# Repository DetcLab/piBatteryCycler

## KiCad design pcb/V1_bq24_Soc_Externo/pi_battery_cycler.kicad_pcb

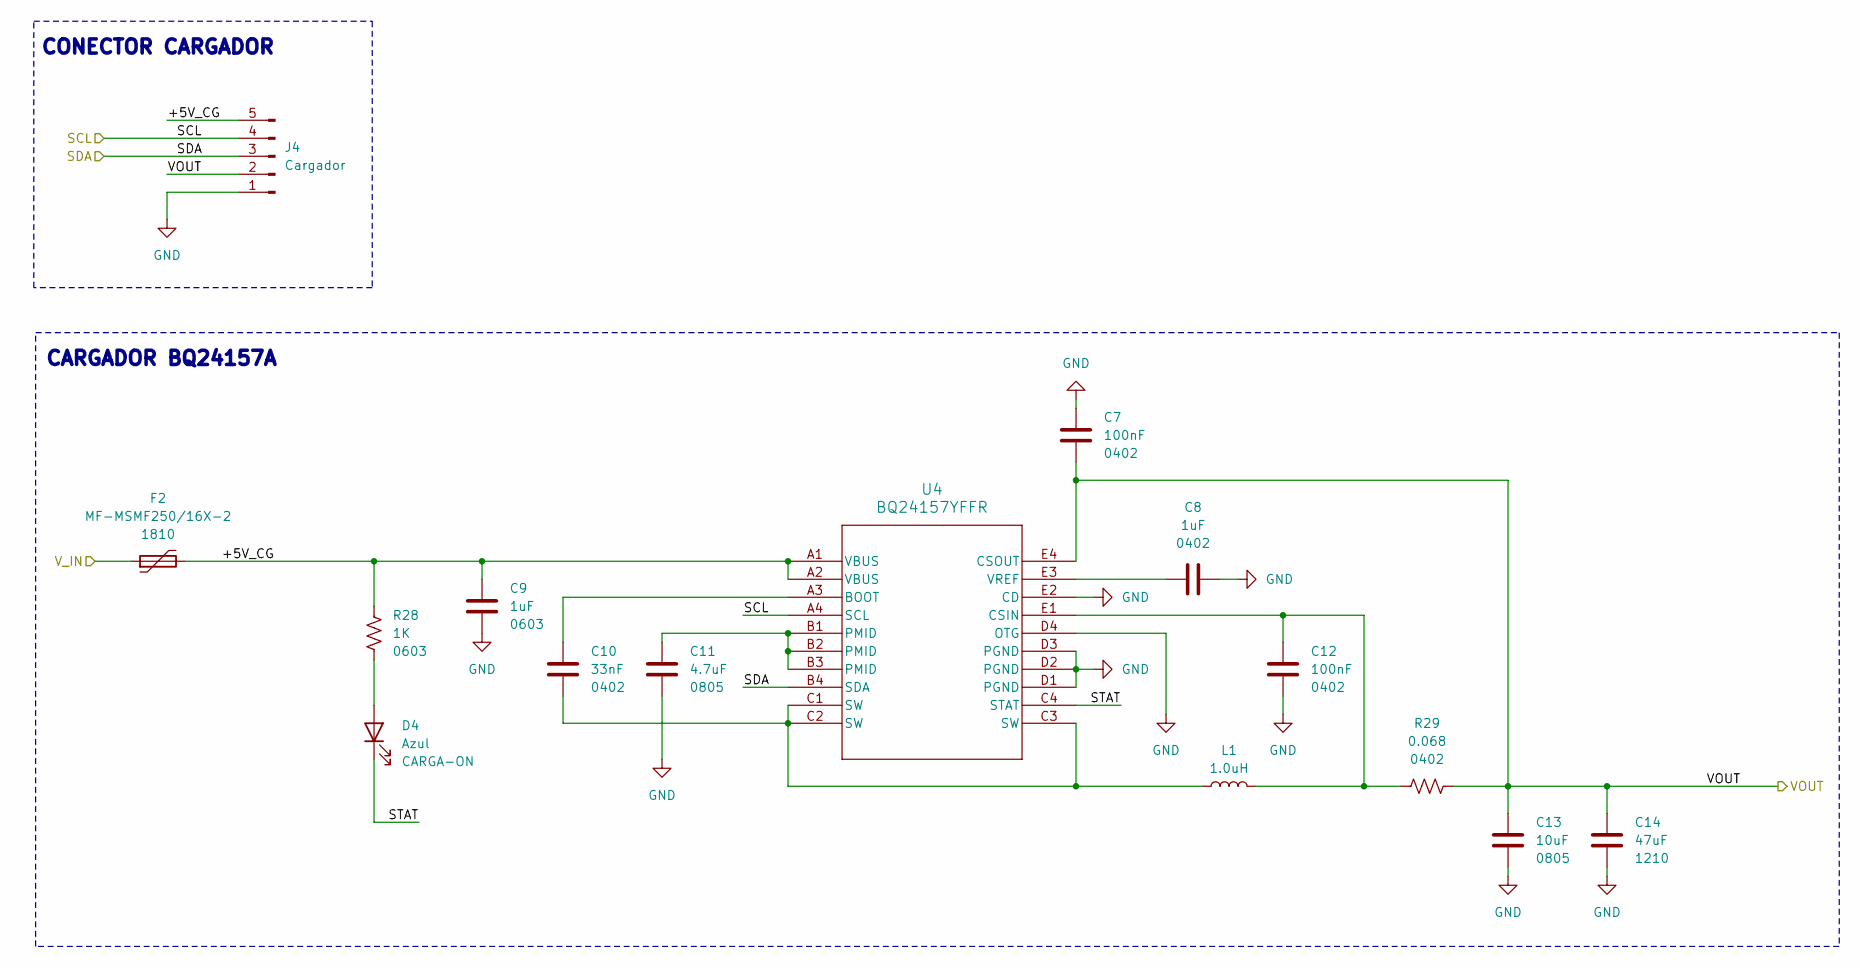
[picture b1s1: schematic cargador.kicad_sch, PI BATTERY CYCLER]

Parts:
C7, C12: 100nF; C_0402_1005Metric; MPN GRM155R71C104KA88D; Digikey 490-3261-2-ND
C8: 1uF; C_0402_1005Metric; MPN CL05A105KP5NNNC; Digikey 1276-1076-2-ND
C9: 1uF; C_0603_1608Metric_Pad1.08x0.95mm_HandSolder; MPN GRM188R61C105KA12D; Digikey 490-10479-2-ND
C10: 33nF; C_0402_1005Metric; MPN GRM155R61C333KA01D; Digikey 490-5416-2-ND
C11: 4.7uF; C_0805_2012Metric; MPN GRM21BR71C475KE51L; Digikey 490-14466-2-ND
C13: 10uF; C_0805_2012Metric; MPN CL21A106KOQNNNE; Digikey 1276-1096-2-ND
C14: 47uF; C_1210_3225Metric; MPN GRM32ER61A476KE20L; Digikey 490-3887-2-ND
D4: Azul; LED_0603_1608Metric; MPN 150060BS75000; Digikey 732-4966-2-ND
F2: MF-MSMF250/16X-2; Fuse_1812_4532Metric; MPN MF-MSMF250/16X-2; Digikey MF-MSMF250/16X-2TR-ND
J4: Cargador; JST_XH_B5B-XH-A_1x05_P2.50mm_Vertical
L1: 1.0uH; L_1008_2520Metric; MPN LQM2HPN1R0MJ0L; Digikey 490-6699-2-ND
R28: 1K; R_0603_1608Metric_Pad0.98x0.95mm_HandSolder; MPN RC0603FR-071KL; Digikey 311-1.00KHRTR-ND
R29: 0.068; R_0402_1005Metric; MPN ERJ-2BWJR068X; Digikey P.068AMTR-ND
U4: BQ24157YFFR; YFF20_TEX; MPN BQ24157YFFR; Digikey 296-39908-2-ND

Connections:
/CARGADOR/+5V_CG: C9.2, F2.2, J4.5, R28.1, U4.A1 (VBUS), U4.A2 (VBUS)
/CARGADOR/SCL: J4.4, U4.A4 (SCL); also elsewhere on the board
/CARGADOR/SDA: J4.3, U4.B4 (SDA); also elsewhere on the board
/CARGADOR/STAT: D4.1 (K), U4.C4 (STAT)
/CARGADOR/VOUT: C7.1, C13.2, C14.2, J4.2, R29.2, U4.E4 (CSOUT); also elsewhere on the board
/CARGADOR/V_IN: F2.1; also elsewhere on the board
GND: C7.2, C8.2, C9.1, C11.2, C12.1, C13.1, C14.1, J4.1, U4.D1 (PGND), U4.D2 (PGND), U4.D3 (PGND), U4.D4 (OTG), U4.E2 (CD); also elsewhere on the board
unnamed: C10.1, L1.1, U4.C1 (SW), U4.C2 (SW), U4.C3 (SW)
unnamed: C11.1, U4.B1 (PMID), U4.B2 (PMID), U4.B3 (PMID)
unnamed: D4.2 (A), R28.2
unnamed: C10.2, U4.A3 (BOOT)
unnamed: C12.2, L1.2, R29.1, U4.E1 (CSIN)
unnamed: C8.1, U4.E3 (VREF)

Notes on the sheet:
CONECTOR CARGADOR
CARGADOR BQ24157A

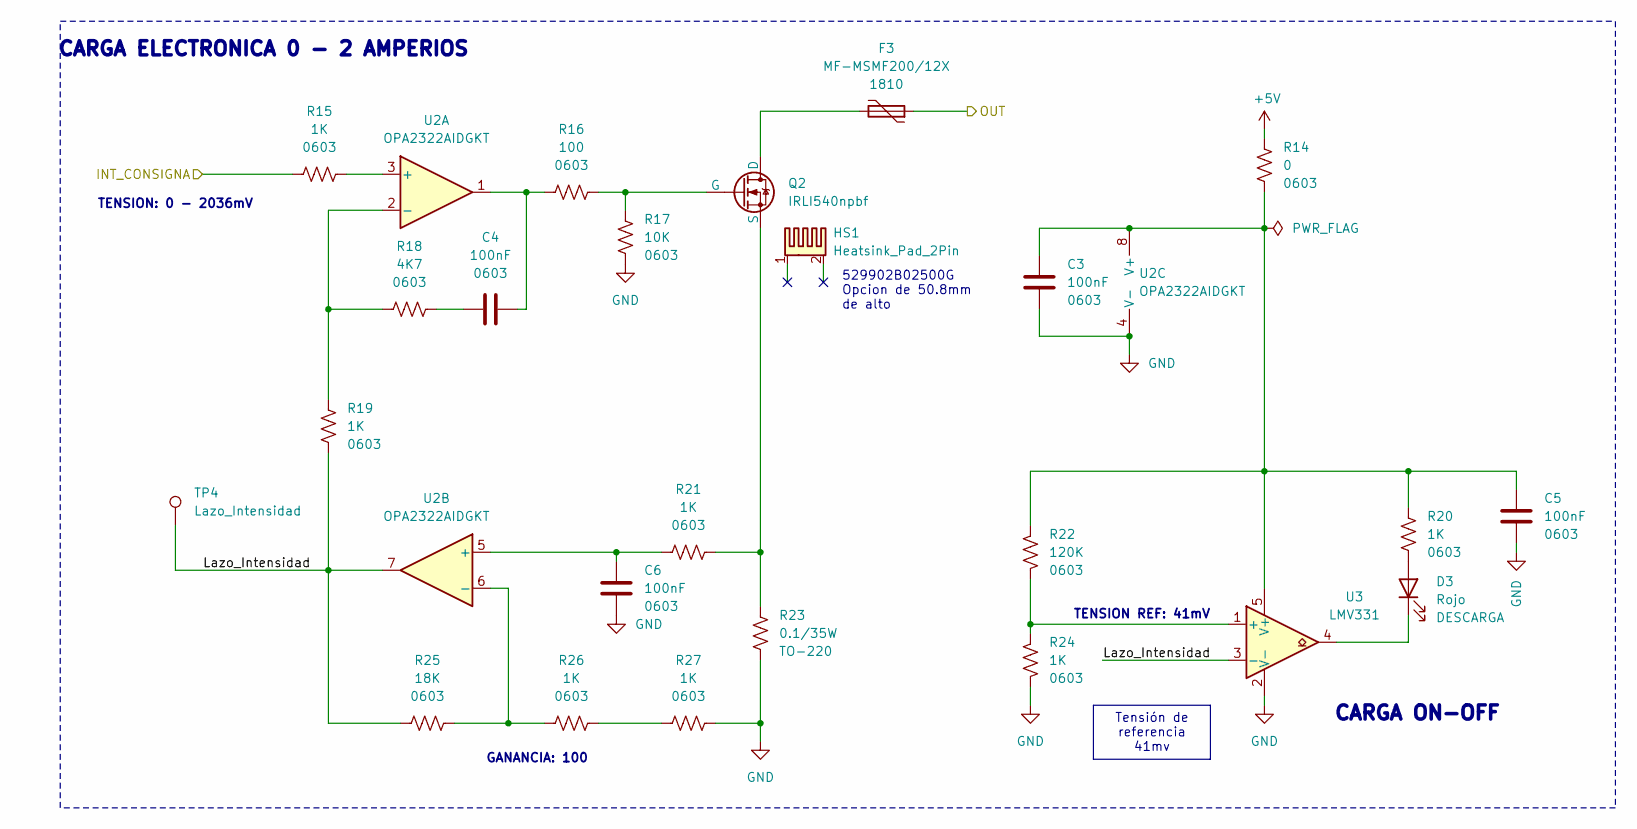
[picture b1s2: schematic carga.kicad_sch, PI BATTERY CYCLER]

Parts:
C3, C4, C5, C6: 100nF; C_0603_1608Metric_Pad1.08x0.95mm_HandSolder; MPN CL10B104KB8NNNC; Digikey 1276-1000-2-ND
D3: Rojo; LED_0603_1608Metric; MPN 150060RS75000; Digikey 732-4978-2-ND
F3: MF-MSMF200/12X; Fuse_1812_4532Metric; MPN MF-MSMF200/12X-2; Digikey 118-MF-MSMF200/12X-2TR-ND
HS1: Heatsink_Pad_2Pin; Heatsink_25.4x41.91mm_Aavid_529802B02500G; Digikey HS374-ND
Q2: IRLI540npbf; TO-220-3_Vertical; Digikey IRL540NPBF-ND
R14: 0; R_0603_1608Metric_Pad0.98x0.95mm_HandSolder; MPN RC0603FR-070RL; Digikey 311-0.0HRTR-ND
R15, R19, R20, R21, R24, R26, R27: 1K; R_0603_1608Metric_Pad0.98x0.95mm_HandSolder; MPN RC0603FR-071KL; Digikey 311-1.00KHRTR-ND
R16: 100; R_0603_1608Metric_Pad0.98x0.95mm_HandSolder; MPN RC0603FR-07100RL; Digikey 311-100HRTR-ND
R17: 10K; R_0603_1608Metric_Pad0.98x0.95mm_HandSolder; MPN RC0603FR-0710KL; Digikey 311-10.0KHRTR-ND
R18: 4K7; R_0603_1608Metric_Pad0.98x0.95mm_HandSolder; MPN RC0603FR-074K7L; Digikey 311-4.70KHRTR-ND
R22: 120K; R_0603_1608Metric_Pad0.98x0.95mm_HandSolder; MPN RC0603FR-07120KL; Digikey 311-120KHRTR-ND
R23: 0.1/35W; TO-220-2_Vertical; Digikey 696-1161-ND
R25: 18K; R_0603_1608Metric_Pad0.98x0.95mm_HandSolder; MPN RC0603FR-0718KL; Digikey 311-18.0KHRTR-ND
TP4: Lazo_Intensidad; TestPoint_Pad_D1.0mm
U2: OPA2322AIDGKT; VSSOP-8_3x3mm_P0.65mm; MPN OPA2322AIDGKT; Digikey 296-28774-2-ND
U3: LMV331; SOT-353_SC-70-5; MPN LMV331IDCKR; Digikey 296-6634-2-ND

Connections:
+5V: R14.1; also elsewhere on the board
/CARGA/INT_CONSIGNA: R15.2; also elsewhere on the board
/CARGA/Lazo_Intensidad: R19.2, R25.2, TP4.1 (1_1), U2.7, U3.3 (-)
/CARGADOR/VOUT: F3.1; also elsewhere on the board
GND: C3.2, C5.2, C6.2, R17.1, R23.2, R24.2, R27.1, U2.4 (V-), U3.2 (V-); also elsewhere on the board
unnamed: C4.1, R18.2
unnamed: C4.2, R16.1, U2.1
unnamed: D3.2 (A), R20.2
unnamed: D3.1 (K), U3.4
unnamed: F3.2, Q2.2 (D)
unnamed: Q2.1 (G), R16.2, R17.2
unnamed: Q2.3 (S), R21.1, R23.1
unnamed: R26.1, R27.2
unnamed: R15.1, U2.3 (+)
unnamed: R18.1, R19.1, U2.2 (-)
unnamed: C6.1, R21.2, U2.5 (+)
unnamed: R25.1, R26.2, U2.6 (-)
unnamed: C3.1, C5.1, R14.2, R20.1, R22.1, U2.8 (V+), U3.5 (V+)
unnamed: R22.2, R24.1, U3.1 (+)

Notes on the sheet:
529902B02500G Opcion de 50.8mm de alto
TENSION: 0 - 2036mV
CARGA ELECTRONICA 0 - 2 AMPERIOS
CARGA ON-OFF
TENSION REF: 41mV
GANANCIA: 100
Tensión de referencia 41mv

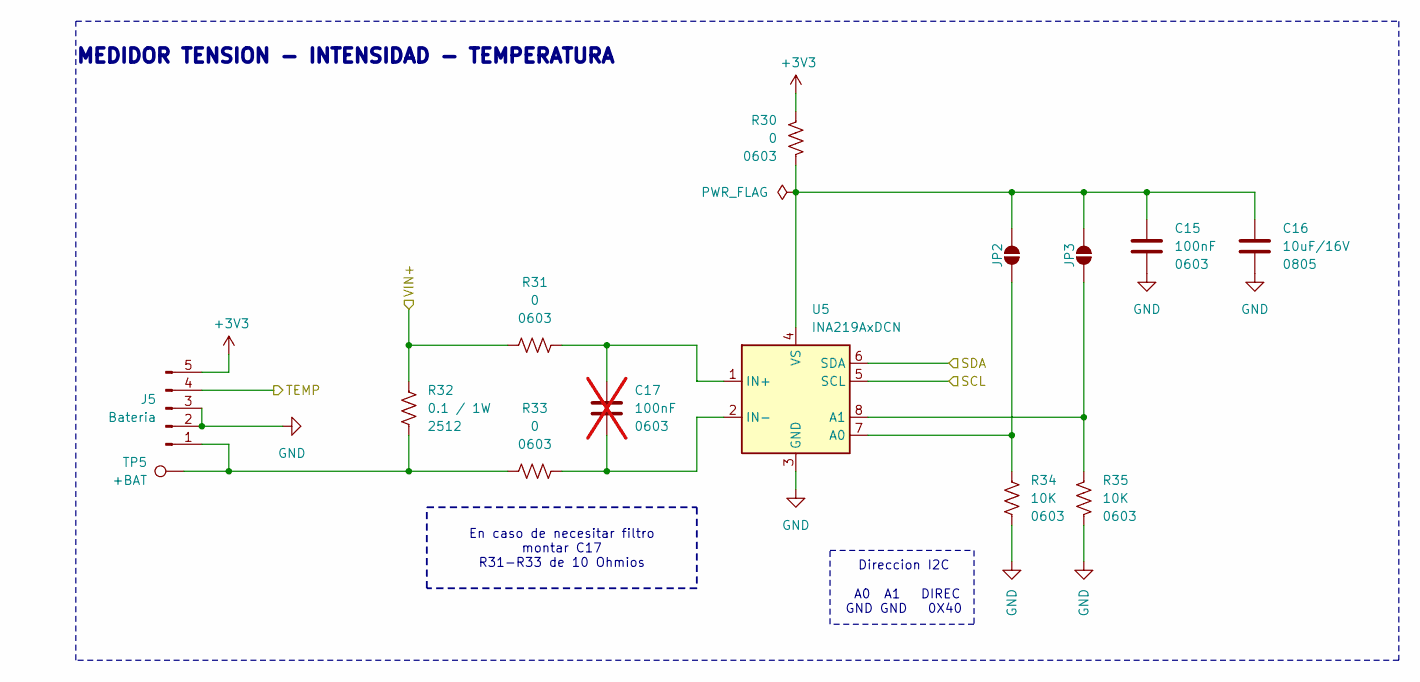
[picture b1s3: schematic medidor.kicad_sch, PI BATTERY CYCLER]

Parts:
C15: 100nF; C_0603_1608Metric_Pad1.08x0.95mm_HandSolder; MPN CL10B104KB8NNNC; Digikey 1276-1000-2-ND
C16: 10uF/16V; C_0805_2012Metric; MPN CL21A106KOQNNNE; Digikey 1276-1096-2-ND
C17: 100nF; C_0603_1608Metric_Pad1.08x0.95mm_HandSolder; MPN CL10B104KB8NNNC; Digikey 1276-1000-2-ND; not fitted
J5: Bateria; JST_XH_B5B-XH-A_1x05_P2.50mm_Vertical
JP2, JP3: SolderJumper_2_Open; SolderJumper-2_P1.3mm_Open_RoundedPad1.0x1.5mm
R30, R31, R33: 0; R_0603_1608Metric_Pad0.98x0.95mm_HandSolder; MPN RC0603FR-070RL; Digikey 311-0.0HRTR-ND
R32: 0.1 / 1W; R_2512_6332Metric; Part Number PE2512FKE070R1L; Digikey YAG2159TR-ND
R34, R35: 10K; R_0603_1608Metric_Pad0.98x0.95mm_HandSolder; MPN RC0603FR-0710KL; Digikey 311-10.0KHRTR-ND
TP5: +BAT; TestPoint_Pad_D1.0mm
U5: INA219AxDCN; SOT-23-8

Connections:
+3V3: J5.5, R30.1; also elsewhere on the board
/CARGADOR/SCL: U5.5 (SCL); also elsewhere on the board
/CARGADOR/SDA: U5.6 (SDA); also elsewhere on the board
/CARGADOR/VOUT: R31.1, R32.1; also elsewhere on the board
/MEDIDOR/TEMP: J5.4; also elsewhere on the board
GND: C15.2, C16.2, J5.2, J5.3, R34.2, R35.2, U5.3 (GND); also elsewhere on the board
unnamed: J5.1, R32.2, R33.1, TP5.1 (1_1)
unnamed: JP2.1 (A), R34.1, U5.7 (A0)
unnamed: C15.1, C16.1, JP2.2 (B), JP3.2 (B), R30.2, U5.4 (VS)
unnamed: JP3.1 (A), R35.1, U5.8 (A1)
unnamed: C17.2, R31.2, U5.1 (IN+)
unnamed: C17.1, R33.2, U5.2 (IN-)

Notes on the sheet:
Direccion I2C A0 A1 DIREC GND GND 0X40
MEDIDOR TENSION - INTENSIDAD - TEMPERATURA
En caso de necesitar filtro montar C17 R31-R33 de 10 Ohmios

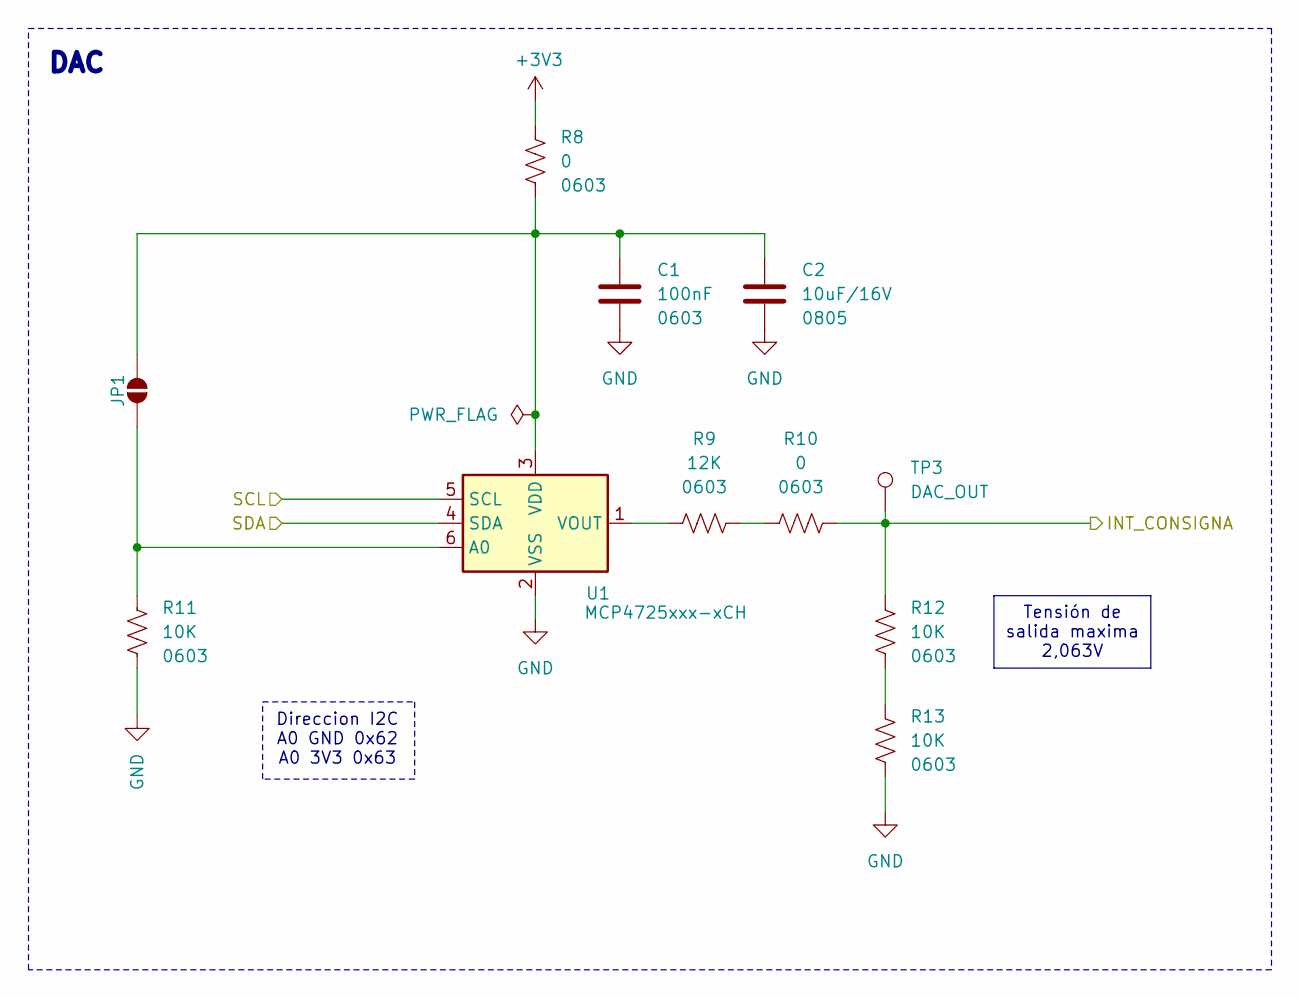
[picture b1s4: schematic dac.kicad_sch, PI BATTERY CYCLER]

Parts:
C1: 100nF; C_0603_1608Metric_Pad1.08x0.95mm_HandSolder; MPN CL10B104KB8NNNC; Digikey 1276-1000-2-ND
C2: 10uF/16V; C_0805_2012Metric; MPN CL21A106KOQNNNE; Digikey 1276-1096-2-ND
JP1: SolderJumper_2_Open; SolderJumper-2_P1.3mm_Open_RoundedPad1.0x1.5mm
R8, R10: 0; R_0603_1608Metric_Pad0.98x0.95mm_HandSolder; MPN RC0603FR-070RL; Digikey 311-0.0HRTR-ND
R9: 12K; R_0603_1608Metric_Pad0.98x0.95mm_HandSolder; MPN RC0603FR-0712KL; Digikey 311-12.0KHRTR-ND
R11, R12, R13: 10K; R_0603_1608Metric_Pad0.98x0.95mm_HandSolder; MPN RC0603FR-0710KL; Digikey 311-10.0KHRTR-ND
TP3: DAC_OUT; TestPoint_Pad_D1.0mm
U1: MCP4725xxx-xCH; SOT-23-6; MPN MCP4725A0T-E/CH; Digikey MCP4725A0T-E/CHCT-ND

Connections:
+3V3: R8.1; also elsewhere on the board
/CARGA/INT_CONSIGNA: R10.2, R12.2, TP3.1 (1_1); also elsewhere on the board
/CARGADOR/SCL: U1.5 (SCL); also elsewhere on the board
/CARGADOR/SDA: U1.4 (SDA); also elsewhere on the board
GND: C1.2, C2.2, R11.2, R13.1, U1.2 (VSS); also elsewhere on the board
unnamed: JP1.1 (A), R11.1, U1.6 (A0)
unnamed: C1.1, C2.1, JP1.2 (B), R8.2, U1.3 (VDD)
unnamed: R9.2, R10.1
unnamed: R12.1, R13.2
unnamed: R9.1, U1.1 (VOUT)

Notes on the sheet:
DAC
Direccion I2C A0 GND 0x62 A0 3V3 0x63
Tensión de salida maxima 2,063V

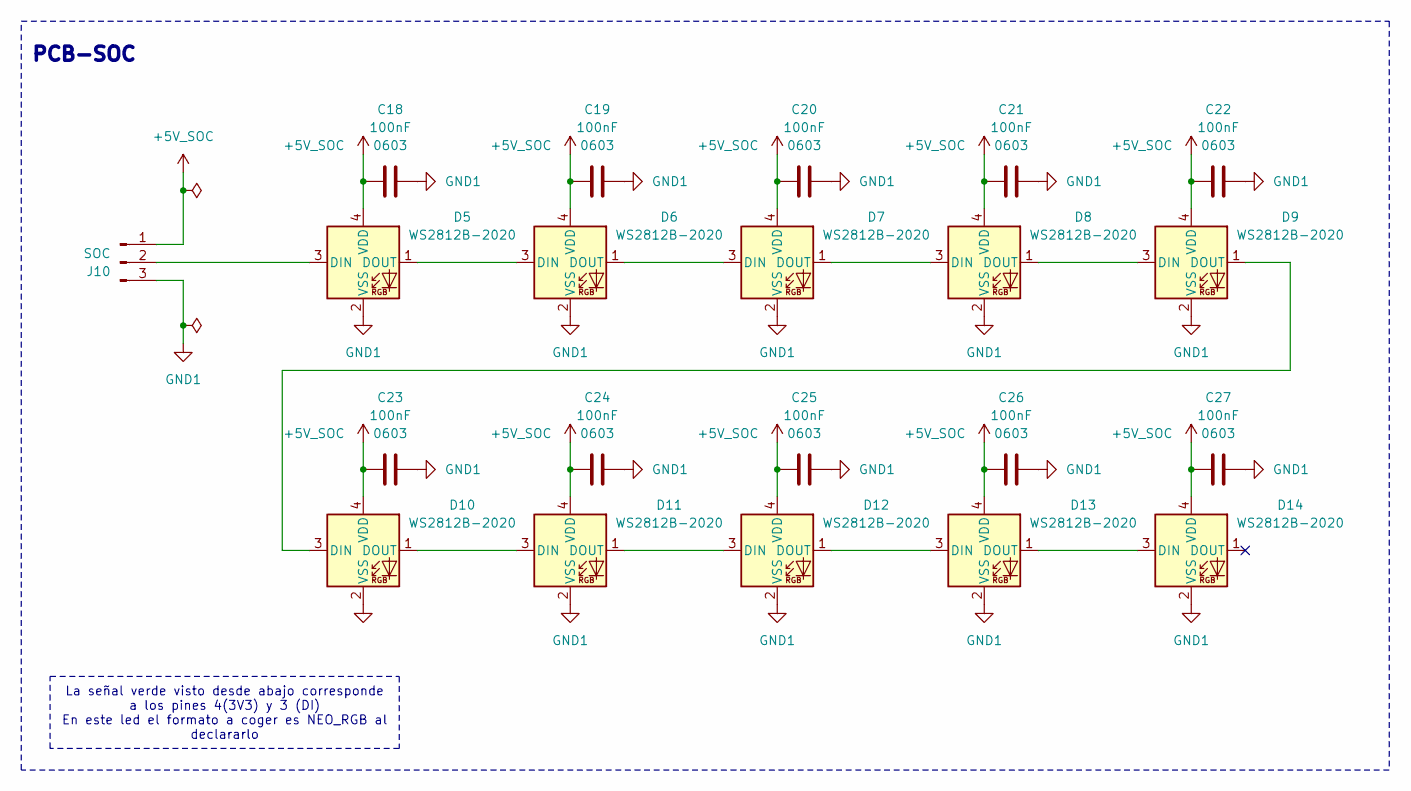
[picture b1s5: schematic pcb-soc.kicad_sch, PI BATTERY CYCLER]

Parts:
C18, C19, C20, C21, C22, C23, C24, C25, C26, C27: 100nF; C_0603_1608Metric_Pad1.08x0.95mm_HandSolder; MPN CL10B104KB8NNNC; Digikey 1276-1000-2-ND
D5, D6, D7, D8, D9, D10, D11, D12, D13, D14: WS2812B-2020; LED_WS2812B-2020_PLCC4_2.0x2.0mm; MPN 4684; Digikey 1528-4684-ND
J10: SOC; PinHeader_1x03_P2.54mm_Vertical

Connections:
+5V_SOC: C18.1, C19.1, C20.1, C21.1, C22.1, C23.1, C24.1, C25.1, C26.1, C27.1, D5.4 (VDD), D6.4 (VDD), D7.4 (VDD), D8.4 (VDD), D9.4 (VDD), D10.4 (VDD), D11.4 (VDD), D12.4 (VDD), D13.4 (VDD), D14.4 (VDD), J10.1
GND1: C18.2, C19.2, C20.2, C21.2, C22.2, C23.2, C24.2, C25.2, C26.2, C27.2, D5.2 (VSS), D6.2 (VSS), D7.2 (VSS), D8.2 (VSS), D9.2 (VSS), D10.2 (VSS), D11.2 (VSS), D12.2 (VSS), D13.2 (VSS), D14.2 (VSS), J10.3
unnamed: D5.3 (DIN), J10.2
unnamed: D5.1 (DOUT), D6.3 (DIN)
unnamed: D6.1 (DOUT), D7.3 (DIN)
unnamed: D7.1 (DOUT), D8.3 (DIN)
unnamed: D8.1 (DOUT), D9.3 (DIN)
unnamed: D9.1 (DOUT), D10.3 (DIN)
unnamed: D10.1 (DOUT), D11.3 (DIN)
unnamed: D11.1 (DOUT), D12.3 (DIN)
unnamed: D12.1 (DOUT), D13.3 (DIN)
unnamed: D13.1 (DOUT), D14.3 (DIN)

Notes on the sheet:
PCB-SOC
La señal verde visto desde abajo corresponde a los pines 4(3V3) y 3 (DI) En este led el formato a coger es NEO_RGB al declararlo

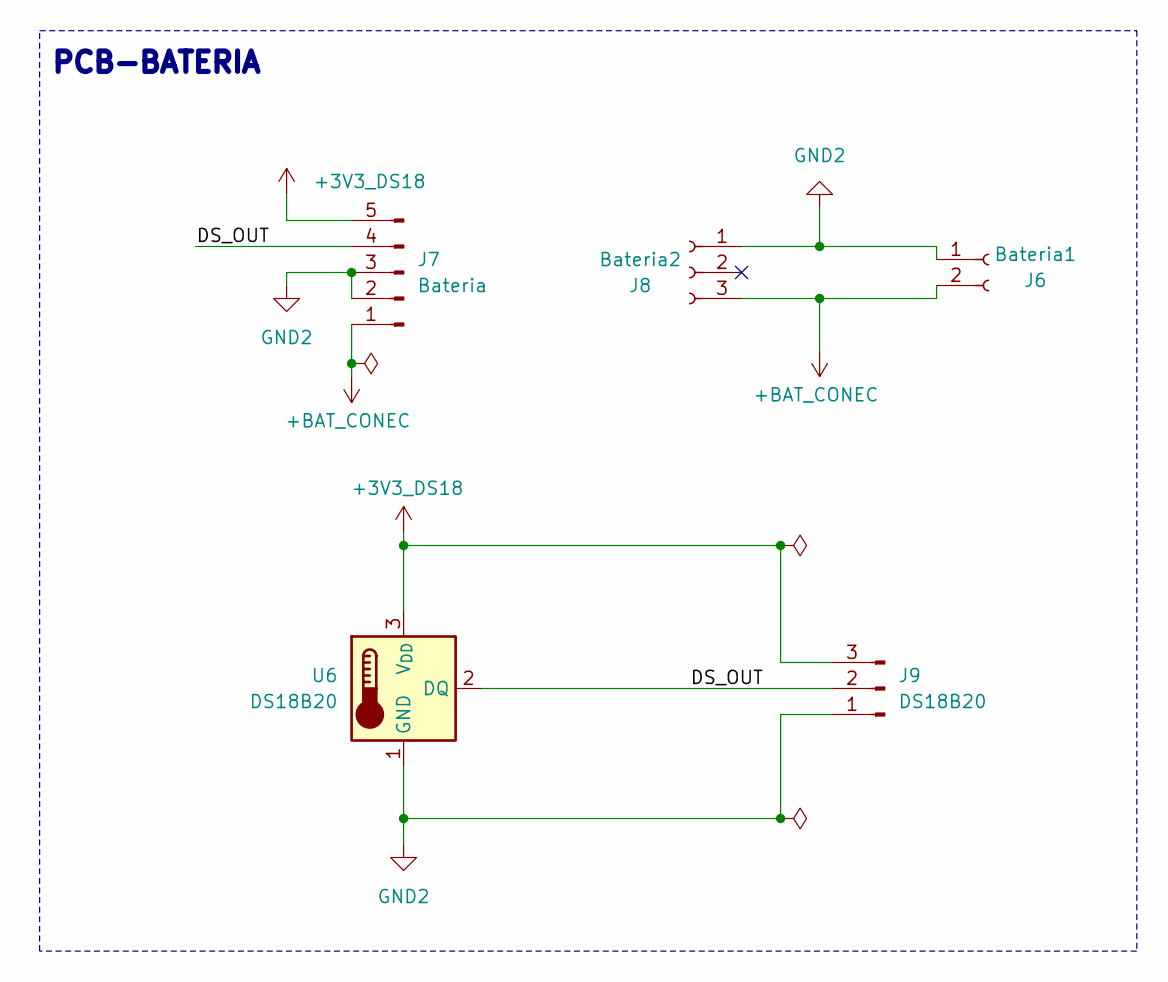
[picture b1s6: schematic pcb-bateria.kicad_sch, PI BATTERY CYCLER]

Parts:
J6: Bateria1; JST_XH_B2B-XH-A_1x02_P2.50mm_Vertical
J7: Bateria; PinHeader_1x05_P2.54mm_Vertical
J8: Bateria2; JST_XH_B3B-XH-A_1x03_P2.50mm_Vertical
J9: DS18B20; PinHeader_1x03_P2.54mm_Vertical
U6: DS18B20; TO-92_Inline; Digikey DS18B20+-ND

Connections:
+3V3_DS18: J7.5, J9.3, U6.3 (V_{DD})
+BAT_CONEC: J6.2, J7.1, J8.3
/PCB-BATERIA/DS_OUT: J7.4, J9.2, U6.2 (DQ)
GND2: J6.1, J7.2, J7.3, J8.1, J9.1, U6.1 (GND)

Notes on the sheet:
PCB-BATERIA

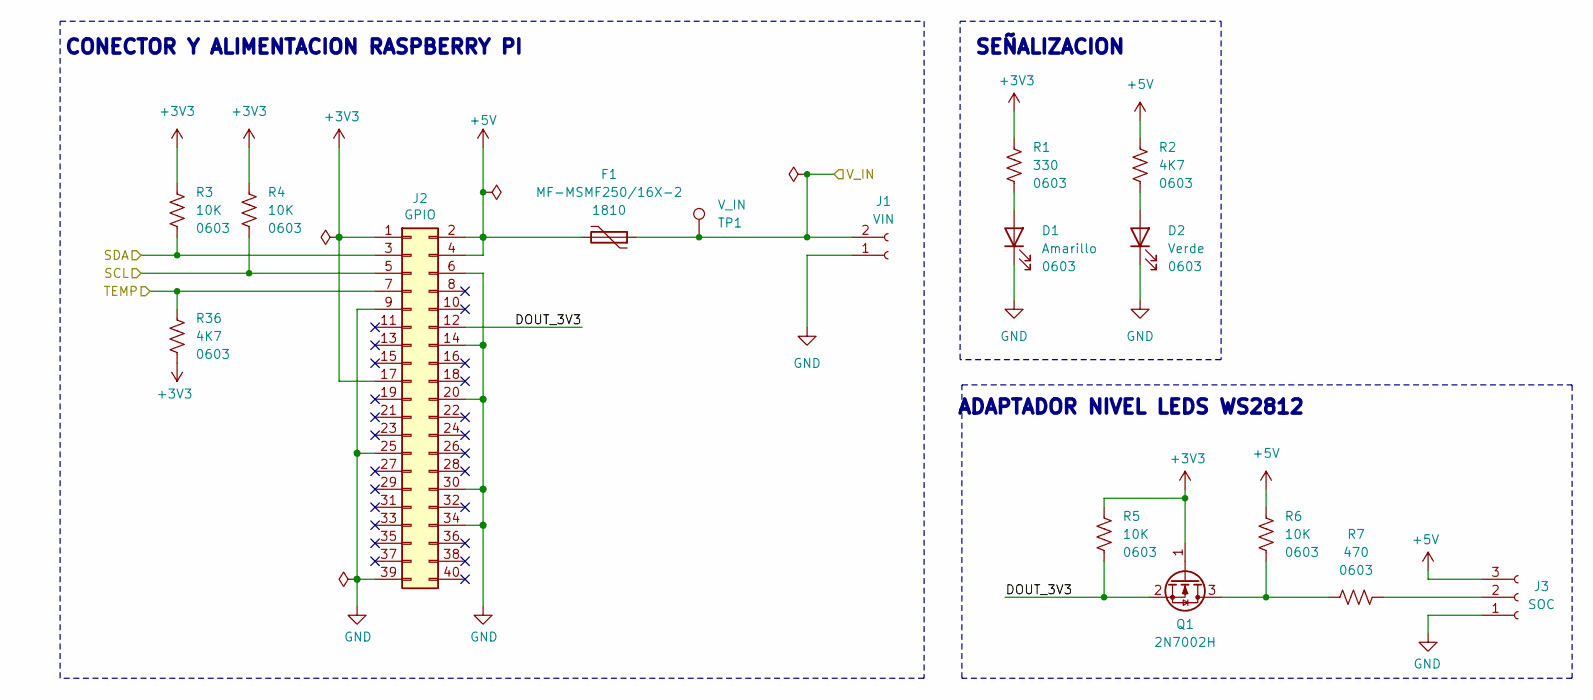
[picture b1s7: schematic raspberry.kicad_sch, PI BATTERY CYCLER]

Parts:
D1: Amarillo; LED_0603_1608Metric; MPN 150060YS75000; Digikey 732-4981-2-ND
D2: Verde; LED_0603_1608Metric; MPN 150060GS75000; Digikey 732-4971-2-ND
F1: MF-MSMF250/16X-2; Fuse_1812_4532Metric; MPN MF-MSMF250/16X-2; Digikey MF-MSMF250/16X-2TR-ND
J1: VIN; CUI_TB006-508-02BE; Digikey 102-6191-ND
J2: GPIO; PinSocket_2x20_P2.54mm_Vertical; Digikey 1528-1783-ND
J3: SOC; JST_XH_B3B-XH-A_1x03_P2.50mm_Vertical
Q1: 2N7002H; SOT-23; MPN 2N7002; Digikey 2N7002NTR-ND
R1: 330; R_0603_1608Metric_Pad0.98x0.95mm_HandSolder; MPN RC0603JR-071K5L; Digikey 311-1.5KGRTR-ND
R2, R36: 4K7; R_0603_1608Metric_Pad0.98x0.95mm_HandSolder; MPN RC0603FR-074K7L; Digikey 311-4.70KHRTR-ND
R3, R4, R5, R6: 10K; R_0603_1608Metric_Pad0.98x0.95mm_HandSolder; MPN RC0603FR-0710KL; Digikey 311-10.0KHRTR-ND
R7: 470; R_0603_1608Metric_Pad0.98x0.95mm_HandSolder; MPN RC0603FR-07470RL; Digikey 311-470HRTR-ND
TP1: V_IN; TestPoint_Pad_D1.0mm

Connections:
+3V3: J2.1, J2.17, Q1.1 (G), R1.1, R3.1, R4.1, R5.1, R36.2; also elsewhere on the board
+5V: F1.2, J2.2, J2.4, J3.3, R2.1, R6.1; also elsewhere on the board
/CARGADOR/SCL: J2.5, R4.2; also elsewhere on the board
/CARGADOR/SDA: J2.3, R3.2; also elsewhere on the board
/CARGADOR/V_IN: F1.1, J1.2, TP1.1 (1_1); also elsewhere on the board
/MEDIDOR/TEMP: J2.7, R36.1; also elsewhere on the board
/RASPBERRY/DOUT_3V3: J2.12, Q1.2 (S), R5.2
GND: D1.1 (K), D2.1 (K), J1.1, J2.6, J2.9, J2.14, J2.20, J2.25, J2.30, J2.34, J2.39, J3.1; also elsewhere on the board
unnamed: D1.2 (A), R1.2
unnamed: D2.2 (A), R2.2
unnamed: J3.2, R7.2
unnamed: Q1.3 (D), R6.2, R7.1

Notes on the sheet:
CONECTOR Y ALIMENTACION RASPBERRY PI
ADAPTADOR NIVEL LEDS WS2812
SEÑALIZACION

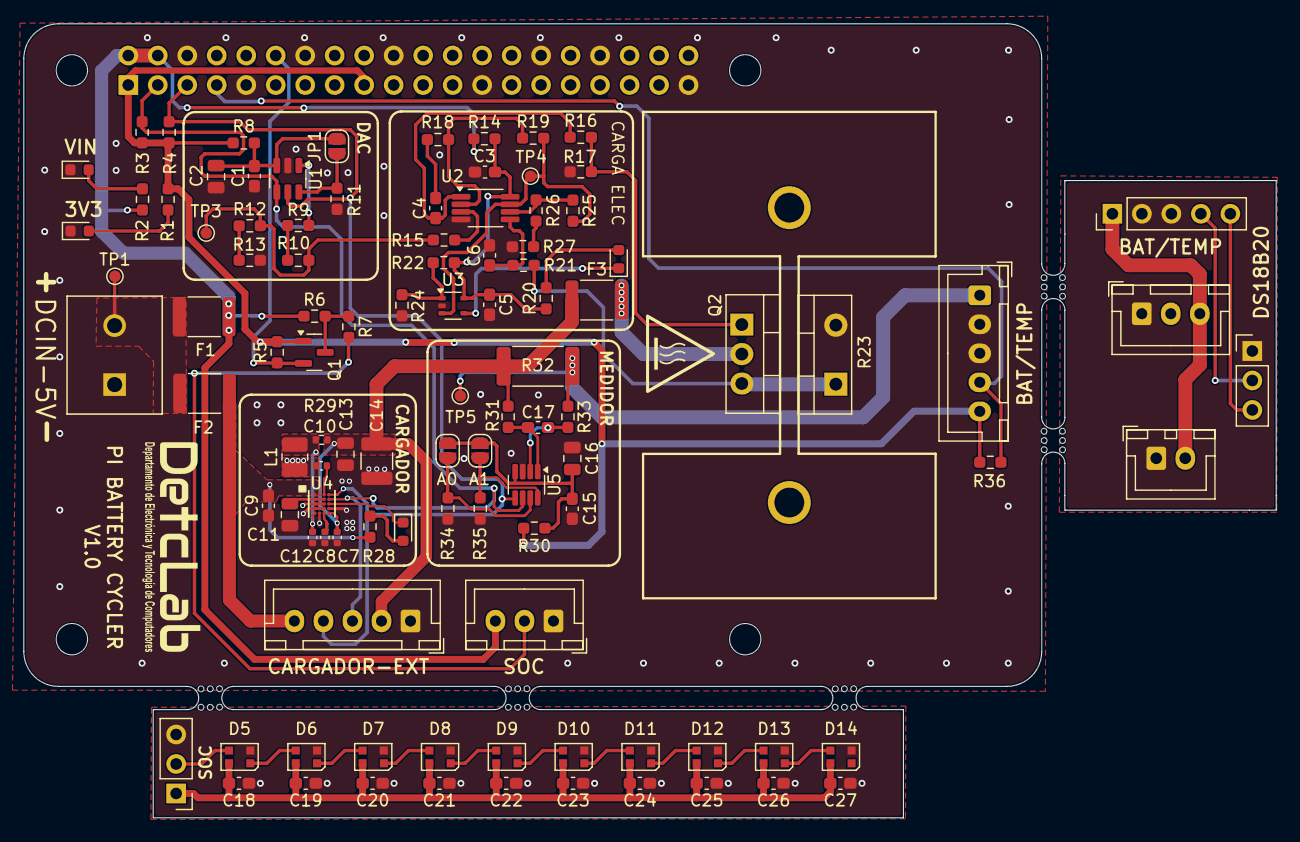
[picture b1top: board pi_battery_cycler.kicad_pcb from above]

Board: 2 copper layers, 107.9 x 68.4 mm, 115 parts (1 on the bottom side), 64 nets.

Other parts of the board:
MH1, MH2, MH3, MH4: MountingHole_2.7mm_M2.5
mouse-bite-2mm-4mm, mouse-bite-2mm-4mm#2, mouse-bite-2mm-4mm#3, mouse-bite-2mm-4mm#4, mouse-bite-2mm-4mm#5: VAL**; mouse-bite-2mm-4mm

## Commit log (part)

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2026-04-12 inicio
2026-04-12 Clase BQ25157
2026-04-12 Modificaciones clase bq25157
2026-04-13 Metodos sets calae BQ25157
2026-04-14 Clase BQ25157 terminada
2026-04-14 Añadido Metodos a clase BQ25157
2026-04-14 Creadas clases DAC y ADC
2026-04-15 prueba clase bq25
2026-04-15 Modificada Cllase BQ25 con Cun clase para los datos
2026-04-16 Clase BQ25157 OK
2026-04-16 Añadiido control led
2026-04-19 Inicio Dashboard
2026-04-28 Modificaciones codigo
2026-05-04 añadido clase ina219
2026-05-14 Añadida clase para controlar sensor 18B20
